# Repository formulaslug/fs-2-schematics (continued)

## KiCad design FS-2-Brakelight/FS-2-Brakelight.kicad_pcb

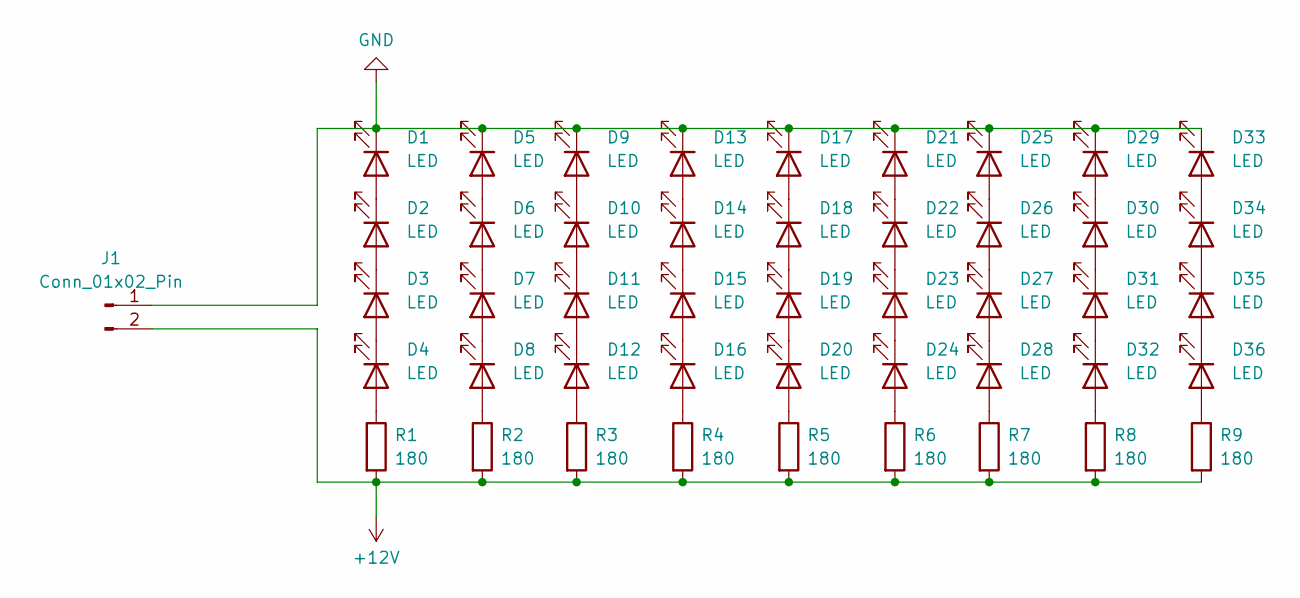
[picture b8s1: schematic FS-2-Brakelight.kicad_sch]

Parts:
D1, D2, D3, D4, D5, D6, D7, D8, D9, D10, D11, D12, D13, D14, D15, D16, D17, D18, D19, D20, D21, D22, D23, D24, D25, D26, D27, D28, D29, D30, D31, D32, D33, D34, D35, D36: LED; LED_D5.0mm
J1: Conn_01x02_Pin; MOLEX_1053091202
R1, R2, R3, R4, R5, R6, R7, R8, R9: 180; R_Axial_DIN0207_L6.3mm_D2.5mm_P10.16mm_Horizontal

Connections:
+12V: J1.2, R1.2, R2.2, R3.2, R4.2, R5.2, R6.2, R7.2, R8.2, R9.2
GND: D1.1 (K), D5.1 (K), D9.1 (K), D13.1 (K), D17.1 (K), D21.1 (K), D25.1 (K), D29.1 (K), D33.1 (K), J1.1
unnamed: D1.2 (A), D2.1 (K)
unnamed: D2.2 (A), D3.1 (K)
unnamed: D3.2 (A), D4.1 (K)
unnamed: D4.2 (A), R1.1
unnamed: D5.2 (A), D6.1 (K)
unnamed: D6.2 (A), D7.1 (K)
unnamed: D7.2 (A), D8.1 (K)
unnamed: D8.2 (A), R2.1
unnamed: D10.2 (A), D11.1 (K)
unnamed: D9.2 (A), D10.1 (K)
unnamed: D11.2 (A), D12.1 (K)
unnamed: D12.2 (A), R3.1
unnamed: D13.2 (A), D14.1 (K)
unnamed: D14.2 (A), D15.1 (K)
unnamed: D15.2 (A), D16.1 (K)
unnamed: D16.2 (A), R4.1
unnamed: D17.2 (A), D18.1 (K)
unnamed: D18.2 (A), D19.1 (K)
unnamed: D19.2 (A), D20.1 (K)
unnamed: D20.2 (A), R5.1
unnamed: D21.2 (A), D22.1 (K)
unnamed: D22.2 (A), D23.1 (K)
unnamed: D23.2 (A), D24.1 (K)
unnamed: D24.2 (A), R6.1
unnamed: D25.2 (A), D26.1 (K)
unnamed: D26.2 (A), D27.1 (K)
unnamed: D27.2 (A), D28.1 (K)
unnamed: D28.2 (A), R7.1
unnamed: D29.2 (A), D30.1 (K)
unnamed: D30.2 (A), D31.1 (K)
unnamed: D31.2 (A), D32.1 (K)
unnamed: D32.2 (A), R8.1
unnamed: D33.2 (A), D34.1 (K)
unnamed: D34.2 (A), D35.1 (K)
unnamed: D35.2 (A), D36.1 (K)
unnamed: D36.2 (A), R9.1

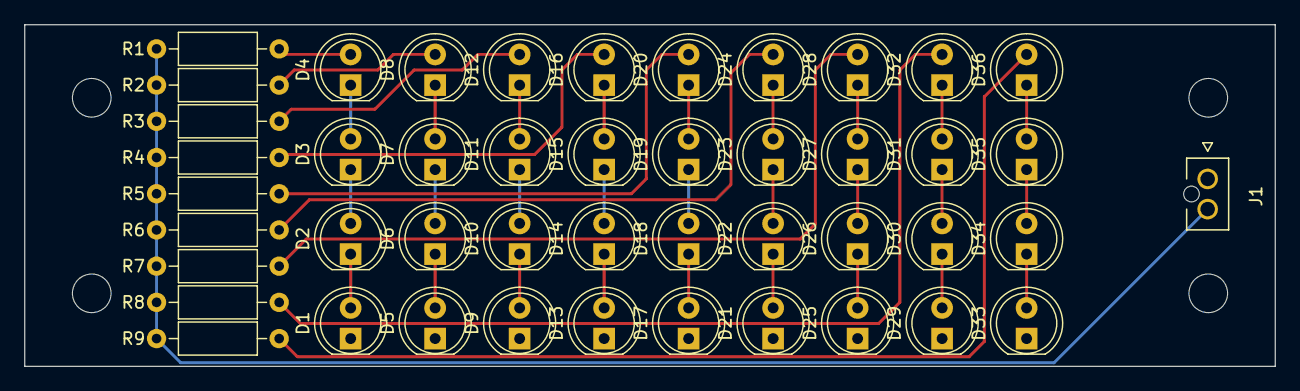
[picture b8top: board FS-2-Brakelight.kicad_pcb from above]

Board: 2 copper layers, 103.6 x 28.3 mm, 46 parts (0 on the bottom side), 38 nets.

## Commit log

2020-08-29 Initialize fs-2-schematics repo
    - Add FSFootprints
    - Add FSSymbols
    - Add BMS schematic
2020-08-29 Add basic readme to project
2020-08-29 Add section on kicad path to README
2020-09-07 Change PCB footprints to be compatible with KiCad 5.1.2
    - Change footprints to new names
    - Remove references to dukeloke libraries
2020-09-07 Move BMS balance sense blocks to subsheet
    - Move all bms balance blocks to copyable subsheet
    - Add 100ohm resistor between bottom voltage tap and C0
2020-09-15 Add FS logo to FSFootprints in multiple DPIs
2020-09-15 Add bms layout v1.0
    - Add layout v1.0 for bms bank
    - Remove on/off switch on bms (not needed)
    - Update resistor values on V+
2020-10-13 Updated README.md for making it easier getting started
2020-10-13 Fixed the links and removed quick start
2020-10-15 uploaded fs-1 tsal design
2020-10-15 removed speaker on the tsal
2020-11-08 fixed footprint library
2020-11-12 Add PTC fusing to BMS board and finish layout v1.0
2020-11-12 Layout v1.1 of BMS
2020-11-16 Add V- plane to BMS module
2020-11-21 Add via to V- resistors on BMS
2024-02-01 Precharge circuit v1
2024-02-03 Added diodes to Precharge PCB
2024-02-03 Discharge board
2024-02-05 Created Acc Board Project
2024-02-05 Fixed file locations for acc board
2024-02-05 Added Edge Cuts to acc board
2024-02-05 added nucleo and linear regulator to acc board
2024-02-06 added micro controller and DCDC
2024-02-06 added iso spi, micro to acc board
2024-02-08 added labels, finished wiring, fixed precharge, added mosfet
2024-02-11 Added BMU sub-board
2024-02-11 Added BSPD and Testing Global sym/ftp libraries
2024-02-12 added descriptions to global symbol library
2024-02-12 Updated BSPD/Acc/PreCh to Global Lib + some Symbol
2024-02-12 Fixed Acc Resistor Footprints
2024-02-12 Moved ACC parts from BSPD to ACC board
2024-02-12 Added labels for ACC board
2024-02-12 Removed ACC parts from BSPD board and organized ACC board schematic
2024-02-12 Added resistors to optocouplers on ACC board
    @goob10000 still needs to determine resistance
2024-02-14 Added most footprints to ACC board
2024-02-14 Minor ACC board fixes
2024-02-14 minimal changes
2024-02-14 small opto datasheet note
2024-02-14 +resistor to optos, +mosfet and timing to BSPD
2024-02-14 Cleaned up resistors on Acc board
2024-02-15 Preliminary pcb design for acc board
2024-02-15 Added 23 pin ampseal connector
2024-02-15 Add lock files to .gitignore
    Lock files shouldn't be included in the repository, because they cause problems opening schematics between machines
2024-02-15 latching relay note
2024-02-15 Fixed acc board large connector
2024-02-15 Minor file fix
2024-02-15 Updated shutdown circuit pins in acc board
2024-02-16 Worked on Acc Board tracks
2024-02-16 APPS/ETC - Initial Commit
    Committing APPS/ETC initial Schema
2024-02-16 Renamed APPS:ETC so that it is a valid path
2024-02-16 Move isolated transformer for BMU on ACC board to bridge GLV and TS
2024-02-17 fixed 555 capacitors
2024-02-17 added correct footprints unarranged to BSPD PCB
2024-02-17 BSPD PCB V1 Done
2024-02-17 schema update
    apps/etc
2024-02-17 apps/schema update
    schema update
2024-02-17 adding more stuff
    schema
2024-02-17 new files for apps.etc
2024-02-17 testing
2024-02-17 updating apps/etc schema
2024-02-18 renaming more files
2024-02-18 schema updates - making progress!
2024-02-18 schema 3/4 done - need connectors in place of HE
2024-02-19 Moved BMU on ACC board
2024-02-19 Added footprints for enclosure connector Add RTDS and TSAL Control Circuit. Add enclosure connections.
2024-02-19 Added more resistors and capacitors to board
2024-02-20 changed bspd boundary to be edge cut
2024-02-20 Minor trace changes to acc board
2024-02-20 All nets connected
2024-02-20 added 3d model for precharge resistor for acc board
2024-02-21 changed lin reg
2024-02-21 added notes to parts of the board that need changing
2024-02-21 fixed mosfets on acc board
2024-02-22 Minor acc board changes
2024-02-22 added op amp / voltage divider for current sensor for acc board
2024-02-22 Fixed op amps for current sensor on acc board
2024-02-23 Moved some shutdown circuit logic from ACC board to pcb
2024-02-23 Merge branch 'master' of github.com:formulaslug/fs-2-schematics
    Updated title to be in title text rather than text
2024-02-23 minor acc changes
2024-02-23 changed BMU connector to 180 degree version and named connectors
2024-02-23 Added footprints for resistors and capacitors
2024-02-23 Update BSPD.kicad_sch
    bspd upadtes
2024-02-24 Changed power block and HVIL power
2024-02-24 Updated for Mosfet, latching, and dash lights
2024-02-24 no changes
2024-02-24 updating BSPD more
2024-02-24 updated lin reg, v div etc.
2024-02-24 Updated timer and connections
2024-02-24 Acc board changes from e meeting
2024-02-24 traces for acc board, WIP
2024-02-25 finished shutdown circuitry
2024-02-25 more traces and fan control for acc board
2024-02-25 Added micro and CAN
2024-02-25 Acc board traces done (for now)
2024-02-25 acc board All traces done and silkscreen improved
2024-02-25 Acc BSPD Split again
2024-02-25 cleared acc stuff
2024-02-26 added latching logic to acc board schematic
2024-02-26 adding charging shutdown to git
2024-02-26 started PCB
2024-02-26 board layout w connectors
2024-02-26 components placed on acc board; traces in progress
2024-02-26 acc board: all traces done; ground plane made
2024-02-26 acc board silkscreen done
2024-02-27 Schematic implementation of current differential circuit
2024-02-27 Compartmentalized some parts of board in diagram
2024-02-27 Fixed sharp angle traces on acc board
2024-02-27 Finished compartmentalization and buffering
2024-02-27 1/2 BSPD Circuitry
2024-02-27 finished board layout
2024-02-27 Silk screen complete
2024-02-27 Moved default kicad models to folder and finished 3d models for board
2024-02-27 fixed minor silkscreen issue
2024-02-27 Made all traces non sharp angles on pads
2024-02-28 Added logo + updated board date
2024-02-28 Finished slug logo and shrunk pcb to size of components
2024-02-28 acc board minor fixes to trace isolation
2024-02-28 updated schema
2024-02-28 acc board minor pcb traces improvements
2024-02-29 for my colead abhi <3
2024-02-29 Linear Reg. CAN. All that
2024-02-29 thug changes
2024-02-29 MORE
2024-02-29 MOREEE
2024-02-29 for my pcb/coding/schema master dwang
2024-02-29 pcb making progress :D
2024-02-29 Acc board CAN fixes
2024-02-29 More ACC board CAN changes
2024-03-01 LEGGO
2024-03-01 app/etc pcb first draft done
2024-03-01 added some 3d models to acc board
2024-03-01 PCB - prototype done
2024-03-01 Fixed stray traces, optocoupler pins, and opto library entry
2024-03-01 more pcb edits(for my wonderful electrical wizard friend dustin!!!!)
2024-03-01 guys wait im goated
    more changes lol sorry for frequent pushes
2024-03-01 Fixed opto letter orientation for soldering
2024-03-01 fixed 5v lin reg pins and trace overlapping holes
2024-03-01 acc board fixed opto footprints
2024-03-01 Minor BSPD hole size fix
2024-03-01 fixed opto silkscreen on acc board
2024-03-02 Updade acc board version #
2024-03-02 pcb debugged
2024-03-02 Fixed crossover traces for SPI on acc board
2024-03-02 added ground plane
2024-03-02 more changes to pcb
2024-03-02 charging changes duhhh
2024-03-04 pcb done!!!
2024-03-04 added name to board
2024-03-04 Acc board changes
2024-03-04 fixed and/nand pins and packages
2024-03-04 fixed nand gate on acc board
2024-03-04 outputed gerber
2024-03-05 Fixed minor schematic bits
2024-03-06 more minor changes to schematic
2024-03-06 more small changes
2024-03-06 more trace and silkscreen fixes
    (sharp angles and overlapping)
2024-03-06 updated opto res #s
2024-03-06 small random updates
2024-03-11 small note to add pull up and down resistors to brake sensor inputs
2024-03-11 fixed note to be only for brakes and not current sensor
2024-03-11 Fixed accumulator board precharge
2024-03-12 charger stuff (don't break plz)
2024-03-16 charger pbc for suree
2024-03-18 added BOM file for Acc board
2024-04-07 fixing charger pcb from sam's comments
2024-04-08 acc board bms miso pull up resistor
2024-04-11 updated opamp datasheets
2024-04-11 fixed tracks !
2024-04-11 footprints, new relay
2024-04-13 bspd inverter -> nand gate (larger)
2024-04-14 backed up stuff? and fixed opamps being backward (power supply)
2024-04-14 Retraced everything to fix opamps
2024-04-14 bspd small changes
2024-04-15 bspd automerge?
2024-04-15 updated pcb
2024-04-15 added rear brake sensor to schamtic
2024-04-15 Fixed latching relay on acc board
2024-04-15 BSPD V2.1 DONE
2024-04-15 100k Pull down resistor for all inputs to MCU pre- opamp
2024-04-15 Add decoupling capacitor to analog inputs. 40 nF for 50 hz sample rate.
2024-04-18 tractive board done
2024-04-18 updated a datasheet
2024-04-18 fixed dk relay symbol
2024-04-18 added new files to LV system
2024-04-20 Added schematic for LV Battery circuitry, Symbols for the LV Battery + DCDC Converter
2024-04-22 small key silkscreen changes (U9 and opto r #s)
2024-04-25 Acc board SPI fixes
2024-04-28 v1.3
    this one for my boy COLE LEWI
2024-04-30 Small buffering updates for current sensor short/open
2024-05-06 brake sensor 5 -> 3.3 V for micro
2024-05-18 old brake light
2024-05-18 Fs-2 backup brakelight
2024-05-18 Mid Updating Tractive Board to Mesh with Github
2024-05-19 Finished Tractive Board Migration
    Archived old tractive board with this symbol "一". Sorts to the end of a list (japanese character). Also symbol library only works with KiCad 8 now
2024-05-20 Added updated old TSAL
2024-05-20 BSPD Version Update
2024-05-24 Updated stuff to latest version
2024-05-29 version update
2024-06-01 Added notes and fixes to optos and relays (Acc + BSPD)
2024-06-02 BSPD fixes
2024-06-03 charging shutdown pcb
2024-06-08 BSPD Relay fix
2024-06-08 Notes + BSPD fixes
    Added a ton of notes about future thoughts and fixes for the board. Also fixed all the major mistakes on the board regarding backwards opamp inputs and voltage dividers (schematic side only)
2024-06-29 added max351 to library and small BSPD changes
2024-06-29 Acc board fixes for version 3
    Still want reverse voltage prevention, fuses, precharge, etc.
2024-06-29 Acc board pcb updated to match schematic
    more silkscreen work to do
2024-06-29 Acc board silkscreen fixes
2024-06-29 Updated Acc board mounting holes and solder pads
2024-07-01 cockpit in, rtds control, and 3.3v and organized.
2024-07-01 Replaced all mf with micro farad
2024-07-02 Added some more information on the silkscreen
2024-07-02 redid silkscreen for apps.etc pcb
2024-07-02 Revert "redid silkscreen for apps.etc pcb"
    This reverts commit d3be66bfebcc9409d1f5c73943bccaf5b70d47f8.
2024-07-02 silk screen update again (please dont break)
2024-07-02 silkscreen final update
2024-07-02 final silkscreen updates
2024-07-07 final silk screen update
2024-07-07 Vias moved off pads. Keep out region around tranceiver. "USB"
2024-07-08 Acc board CDR changes
    Still need test points
2024-07-08 BSPD+ Board Rework
    - Broke main functions into sub-schematics
    - Fixed all known bugs from previous iteration
    1. OPamp reverse polarities
    2. Brake and dash light fixes
    3. Status Lights
    4. Micro wiring fixed to be 3V3 instead of 5V
2024-07-08 Acc Board test points added
2024-07-11 Overhaul of BPSD to V3.0
2024-07-11 Updated Version on PCB and added "USB"
2024-07-12 made PCB (reloaded fill zone)
2024-07-17 Version Number changed to 3.0
2024-07-17 updated version numbers
2024-07-18 Added brake sensor power and ground on schem and pcb
2024-08-01 Repair BMS Symbols
2024-08-14 input output polarity changes on schematic
2024-08-14 Fixed resistance labels of R37 and R38 being switched
2024-08-28 Telemetry Board V1
2024-08-29 Telemetry Board V1
    Also tiny BSPD silk screen change (L432KC instead of LM432KC)
2024-08-29 Telemetry Board V1 Done
2024-09-03 Dash setup file added to repo
2024-09-19 Fixed telem board silkscreen
2024-09-29 moved falstad tests for bspd to fs-2-schematics
2024-10-08 updated version number
2024-10-08 telem board overwrite
2024-10-09 no significant changes
2025-01-10 brakelight ? abd telem board!
2025-04-20 hopefully making the repo smaller?
